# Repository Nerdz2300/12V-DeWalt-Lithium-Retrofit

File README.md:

# 12V DeWalt Lithium Battery Retrofit

## Project Start Date: 5/07/2018

Plan is to rebuild a old/bad DeWalt battery and Retrofit it with some lithium cells that I pulled from a used laptop battery

It will have a 12.6V Charger, +/-20mV Accuracy, 1A charge rate. 2 LEDs, one for Charging, one for Done

Cells will be configured as follows:2 Parallel,3 Series which will give us 12.6V at 4000mAh. Each cell is 2000mAh

Each cell in series will have to be balanced, so a balancer is needed. 

This is untested thusfar, but I have built the main circuit before which does work. Everything else is extra. 

To Do:

* BOM for Charger

* Balancer Circuitry

* Balancer BOM

* Build and Test Charger

* Build and test Balancer

* Build the actual pack

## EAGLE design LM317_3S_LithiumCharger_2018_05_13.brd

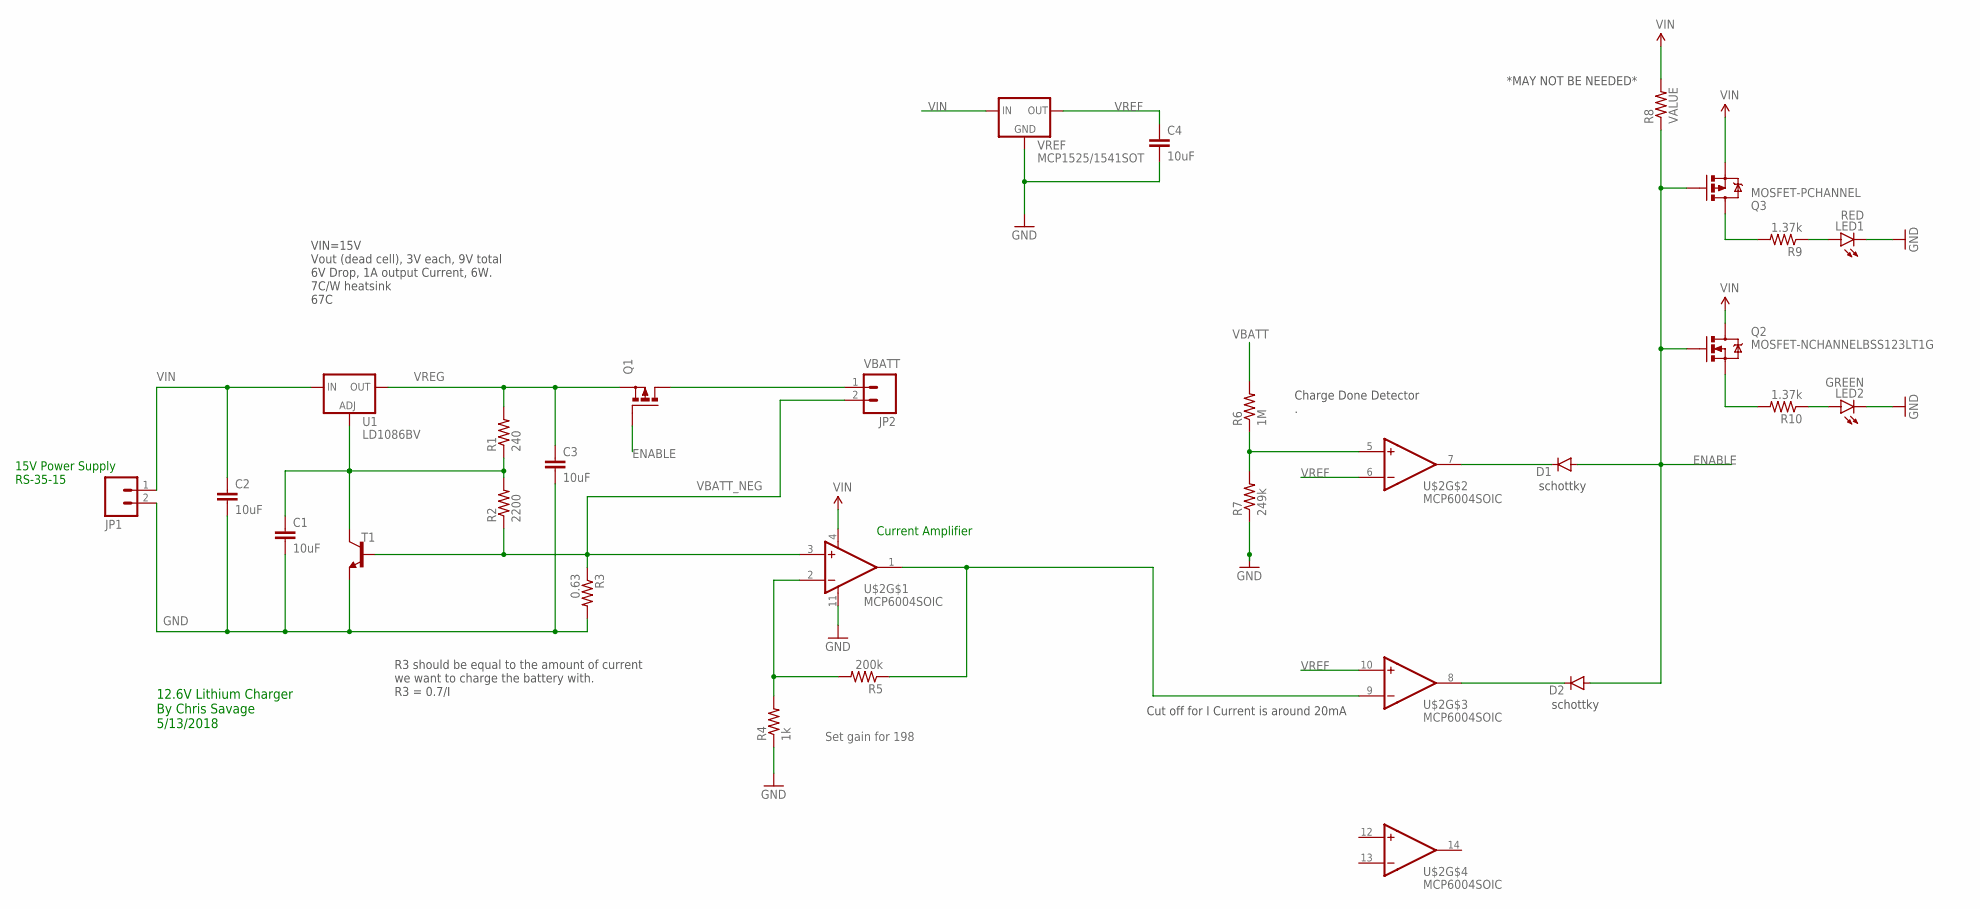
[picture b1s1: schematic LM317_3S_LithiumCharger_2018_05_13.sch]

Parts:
C1, C2, C3, C4: 10uF; 1206
D1, D2: DIODESOD123; SOD-123
JP1, JP2: M02POLAR_LOCK; MOLEX-1X2_LOCK
LED1: RED; LED5MM
LED2: GREEN; LED5MM
Q1: PMOSFET_PTO220BV; TO220BV
Q2: MOSFET-NCHANNELBSS123LT1G; SOT23-3
Q3: MOSFET-PCHANNEL; SOT23-3
R1: 240; 1206
R2: 2200; 1206
R3: 0.63; R2512
R4: 1k; 1206
R5: 200k; 1206
R6: 1M; 1206
R7: 249k; 1206
R8: VALUE; 1206
R9, R10: 1.37k; 1206
T1: MMBT3904LT1-NPN-SOT23-BEC; SOT23-BEC
U1: LD1086BV; 317TS
U$2: MCP6004SOIC; SOIC-14
VREF: MCP1525/1541SOT; SOT23-3

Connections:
ENABLE: D1.A, D2.A, Q1.G, Q2.1 (G), Q3.1 (G), R8.1
GND: C1.2, C2.2, C3.2, C4.2, JP1.2, LED1.K (C), LED2.K (C), R3.2, R4.1, R7.1, T1.E, U$2.11 (V-), VREF.3 (GND)
IOUT: R5.1, U$2.1 (OUT), U$2.9 (-IN)
unnamed: R4.2, R5.2, U$2.2 (-IN)
unnamed: C1.1, R1.1, R2.2, T1.C, U1.1 (ADJ)
unnamed: D1.C, U$2.7 (OUT)
unnamed: R6.1, R7.2, U$2.5 (+IN)
unnamed: LED1.A, R9.1
unnamed: D2.C, U$2.8 (OUT)
unnamed: Q2.2 (S), R10.2
unnamed: Q3.3 (D), R9.2
unnamed: LED2.A, R10.1
VBATT: JP2.1, Q1.D, R6.2
VBATT_NEG: JP2.2, R2.1, R3.1, T1.B, U$2.3 (+IN)
VIN: C2.1, JP1.1, Q2.3 (D), Q3.2 (S), R8.2, U1.3 (IN), U$2.4 (V+), VREF.1 (IN)
VREF: C4.1, U$2.6 (-IN), U$2.10 (+IN), VREF.2 (OUT)
VREG: C3.1, Q1.S, R1.2, U1.2 (OUT)

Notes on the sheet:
Set gain for 198
Current Amplifier
R3 should be equal to the amount of current we want to charge the battery with. R3 = 0.7/I
*MAY NOT BE NEEDED*
schottky
Cut off for I Current is around 20mA
Charge Done Detector .
15V Power Supply RS-35-15
VIN=15V Vout (dead cell), 3V each, 9V total 6V Drop, 1A output Current, 6W. 7C/W heatsink 67C
12.6V Lithium Charger By Chris Savage 5/13/2018

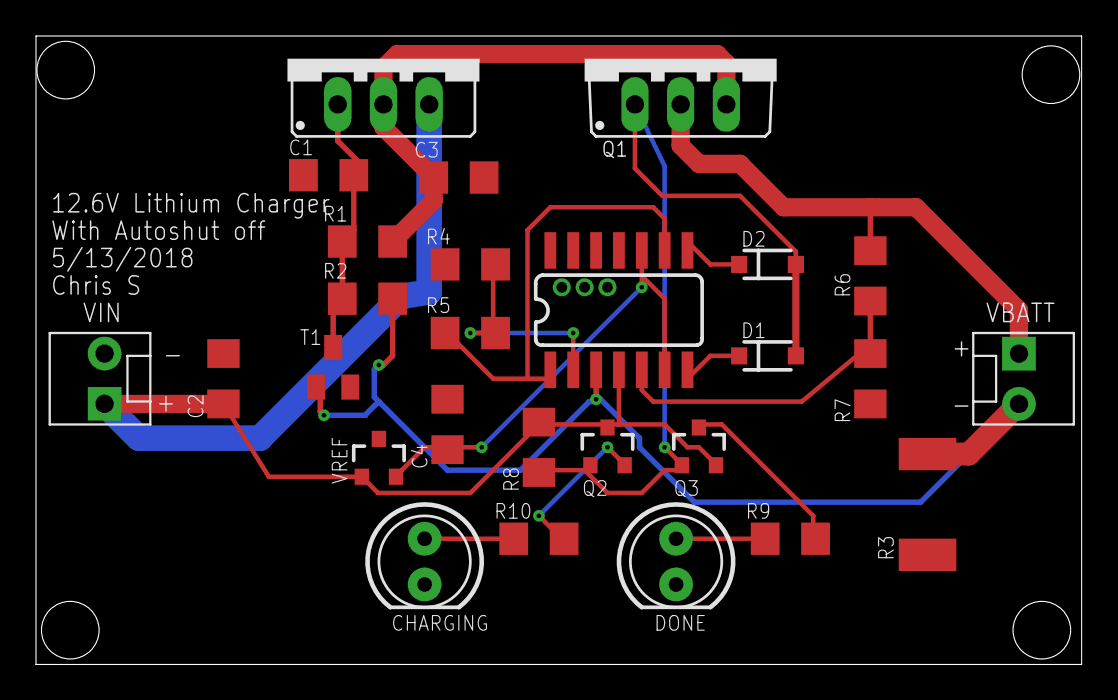
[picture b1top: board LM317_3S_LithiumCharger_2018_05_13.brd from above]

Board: 2 copper layers, 58.1 x 34.9 mm, 27 parts (0 on the bottom side), 17 nets.

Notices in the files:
parts and their libraries:
SparkFun-Capacitors: Licensing: Creative Commons ShareAlike 4.0 International - https://creativecommons.org/licenses/by-sa/4.0
